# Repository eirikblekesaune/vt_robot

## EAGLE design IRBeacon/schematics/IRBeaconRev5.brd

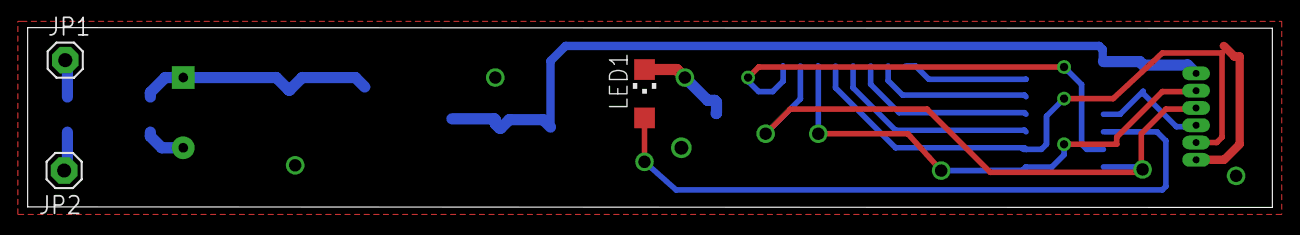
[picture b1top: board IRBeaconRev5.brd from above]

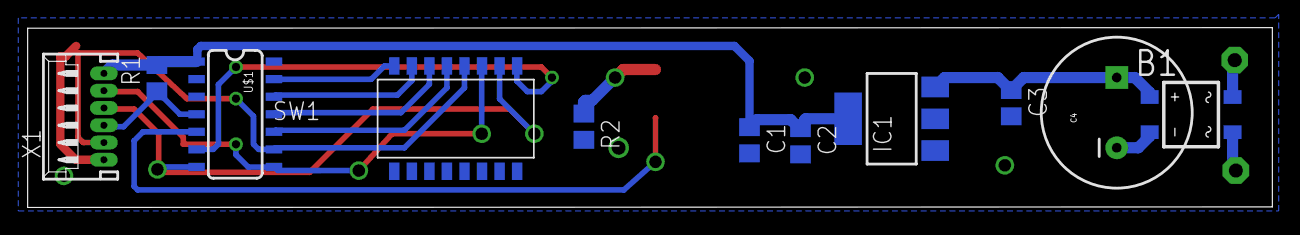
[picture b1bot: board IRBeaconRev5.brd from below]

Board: 2 copper layers, 90.0 x 13.0 mm, 14 parts (11 on the bottom side), 16 nets.

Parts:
B1: B2S; MBS
C1, C3: 0.1uF; C0805
C2: 10uF; C0805
C4: CPOL-RADIAL-1000UF-25V
IC1: LD117AS33TR; SOT223
JP1, JP2: 1X01
LED1: CHIPLED_1206
R1: 10k; R0805
R2: R0805
SW1: 416131160808
U$1: ATTINY84; SO14
X1: 53048-06

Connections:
GND: B1.-, C1.2, C2.2, C3.2, C4.2, IC1.1, R2.2, SW1.1, SW1.2, SW1.3, SW1.4, SW1.5, SW1.6, SW1.7, SW1.8, U$1.14, X1.6
unnamed: R1.1, U$1.4, X1.4
unnamed: B1.AC2, JP2.1
unnamed: B1.+, C3.1, C4.1, IC1.3
unnamed: SW1.15, U$1.12
unnamed: SW1.14, U$1.11
unnamed: SW1.13, U$1.10
unnamed: LED1.A, U$1.5
unnamed: SW1.12, U$1.9, X1.5
unnamed: SW1.10, U$1.7, X1.3
unnamed: SW1.9, U$1.6
unnamed: SW1.16, U$1.13
unnamed: LED1.C, R2.1
unnamed: SW1.11, U$1.8, X1.2
RAIL_A: B1.AC1, JP1.1
VCC: C1.1, C2.1, IC1.4, R1.2, U$1.1, X1.1

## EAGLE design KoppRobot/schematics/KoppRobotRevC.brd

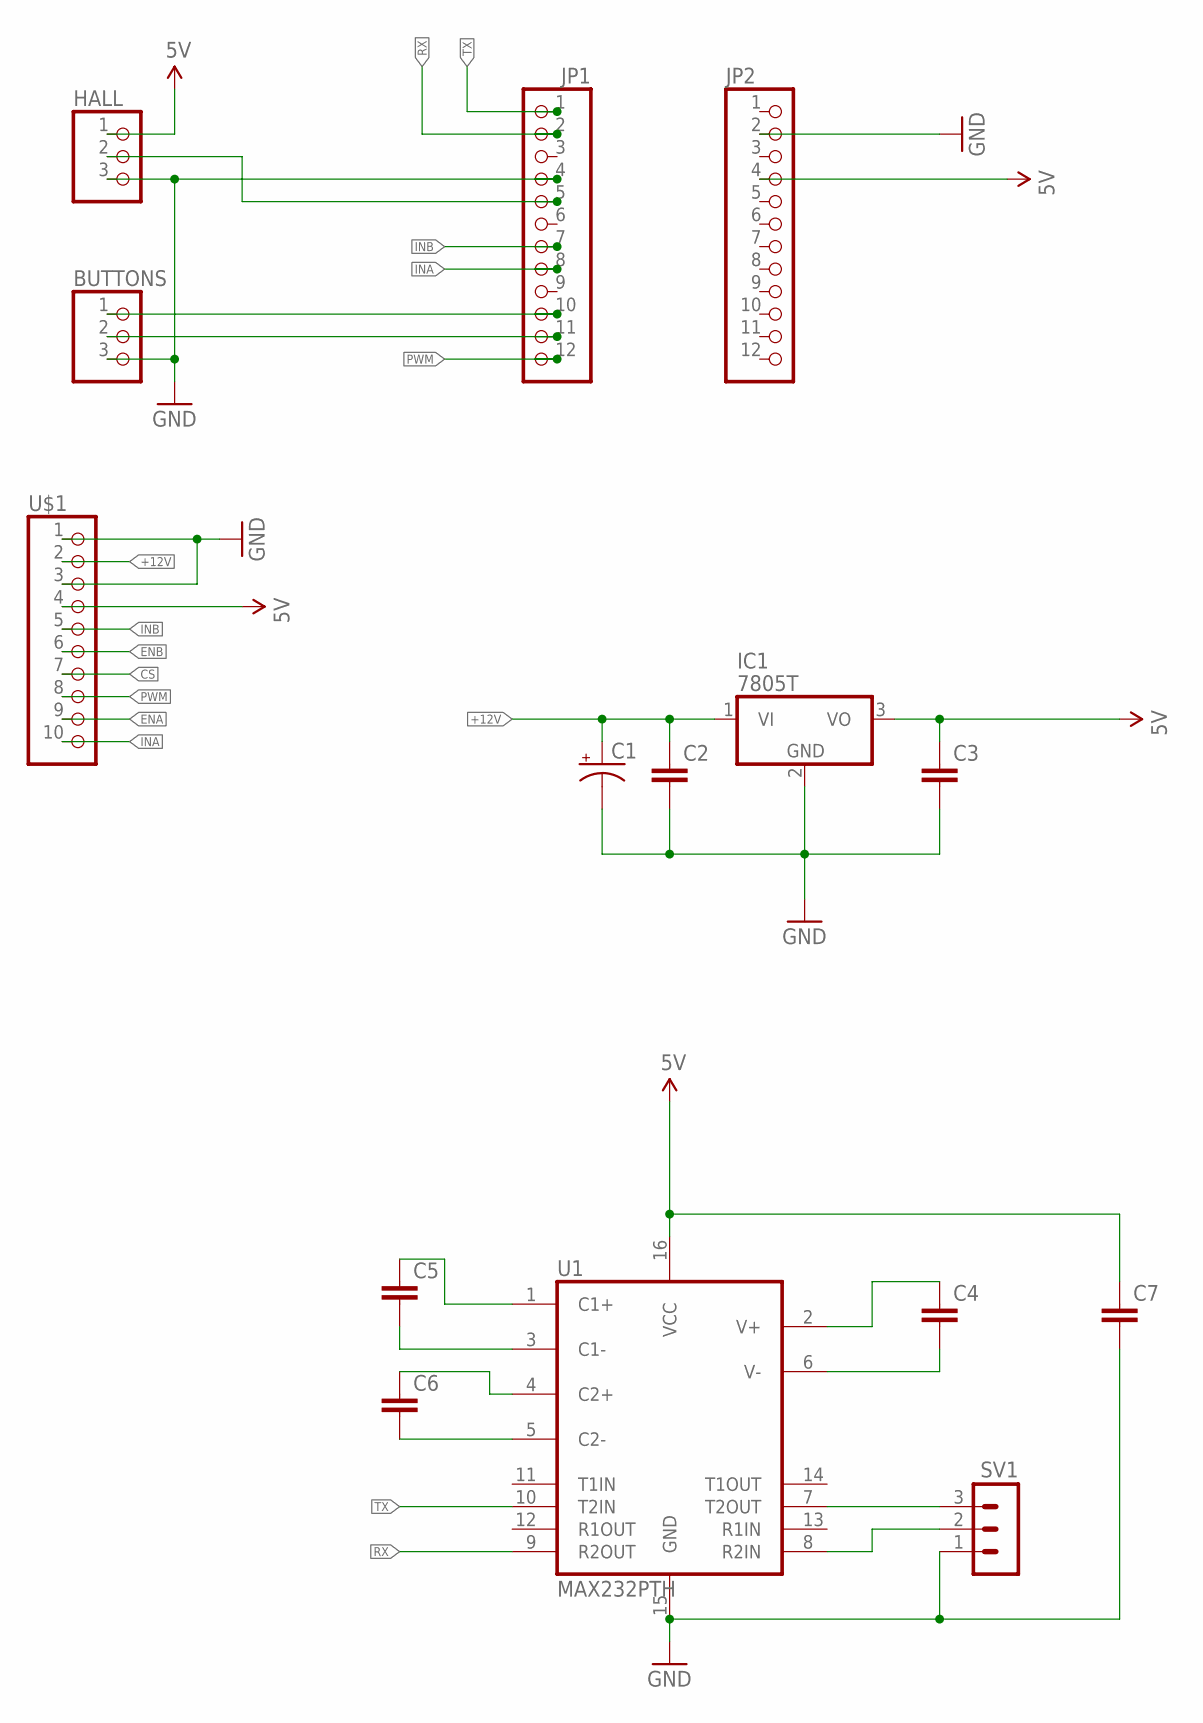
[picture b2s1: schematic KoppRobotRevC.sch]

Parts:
BUTTONS: PINHD-1X3; 1X03
C1: CAP_POLPTH3; CPOL-RADIAL-1000UF-63V
C2, C3, C4, C5, C6, C7: CAP0603-CAP; 0603-CAP
HALL: PINHD-1X3; 1X03
IC1: 7805T; TO220H
JP1, JP2: PINHD-1X12; 1X12
SV1: MA03-1
U1: MAX232PTH; DIL16
U$1: PINHD-1X10; 1X10

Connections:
5V: C3.1, C7.1, HALL.1, IC1.3 (VO), JP2.4, U1.16 (VCC), U$1.4
+12V: C1.1 (+), C2.1, IC1.1 (VI), U$1.2
CS: U$1.7
ENA: U$1.9
ENB: U$1.6
GND: BUTTONS.3, C1.2 (-), C2.2, C3.2, C7.2, HALL.3, IC1.2 (GND), JP1.4, JP2.2, SV1.1, U1.15 (GND), U$1.1, U$1.3
INA: JP1.8, U$1.10
INB: JP1.7, U$1.5
unnamed: C5.1, U1.1 (C1+)
unnamed: C5.2, U1.3 (C1-)
unnamed: C6.1, U1.4 (C2+)
unnamed: C6.2, U1.5 (C2-)
unnamed: C4.2, U1.6 (V-)
unnamed: C4.1, U1.2 (V+)
unnamed: SV1.2, U1.8 (R2IN)
unnamed: SV1.3, U1.7 (T2OUT)
unnamed: BUTTONS.2, JP1.11
unnamed: BUTTONS.1, JP1.10
unnamed: HALL.2, JP1.5
PWM: JP1.12, U$1.8
RX: JP1.2, U1.9 (R2OUT)
TX: JP1.1, U1.10 (T2IN)

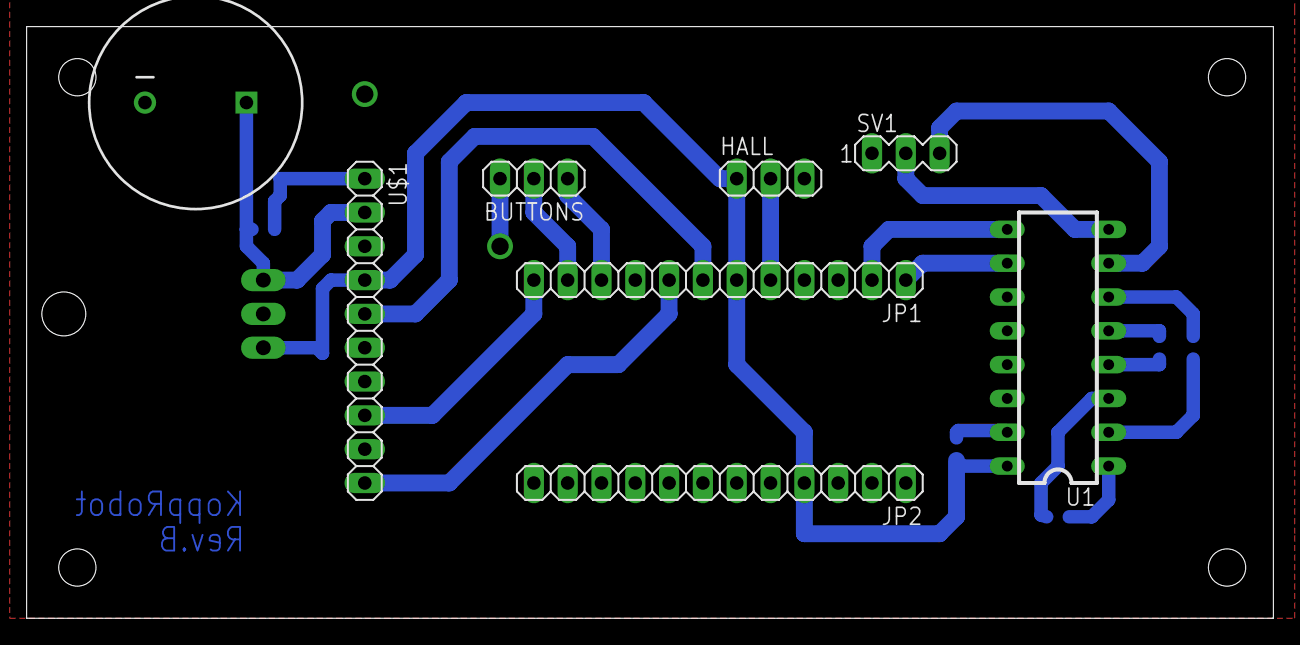
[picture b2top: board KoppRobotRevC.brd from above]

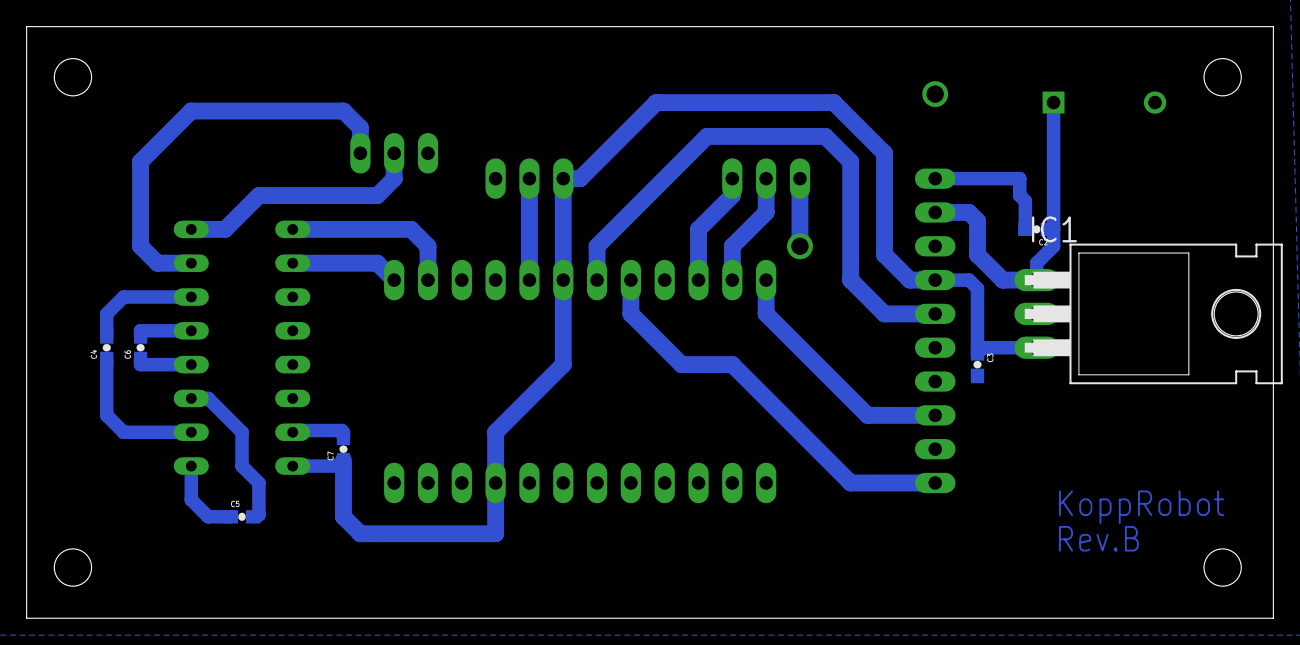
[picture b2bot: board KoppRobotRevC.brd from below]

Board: 2 copper layers, 93.7 x 44.4 mm, 15 parts (7 on the bottom side), 19 nets.

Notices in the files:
parts and their libraries:
DipSchalter: Copyright: Würth Elektronik
SparkFun-DigitalIC: Licensing: CC v3.0 Share-Alike You are welcome to use this library for commercial purposes.
